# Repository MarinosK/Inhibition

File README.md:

### Inhibition ###

Installation | Workshop (c) 2016
by Marinos Koutsomichalis <marinos@marinoskoutsomichalis.com>

Code and hardware designs are distributed under the Attribution-NonCommercial-ShareAlike 3.0 Unported Creative Commons Licence (details here: http://creativecommons.org/licenses/by-nc-sa/3.0/deed.en_US).

> EVERYTHING IN THIS BUNDLE IS DISTRIBUTED AS IS WITH NO GUARANTEE OF FUNCTIONALITY OR RELEVANCE TO THIRD PARTY PROJECTS - THE DEVELOPER IS NOT TO BE HELD RESPONSIBLE FOR PERSONAL INJURIES, HARDWARE, FINANCIAL, OR ANY OTHER LOSSES AND IN GENERAL FOR ANY MISFORTUNATE EVENT CAUSED BY THE DESCRIBED SOFTWARE/HARDWARE OR IN THE PROCESS OF ATTEMPTING TO IMPLEMENT IT. IF YOU DON'T AGREE WITH THE AFOREMENTIONED YOUR ARE NOT ALLOWED TO USE THE MATERIAL PROVIDED HEREIN

# This bundle comprises #

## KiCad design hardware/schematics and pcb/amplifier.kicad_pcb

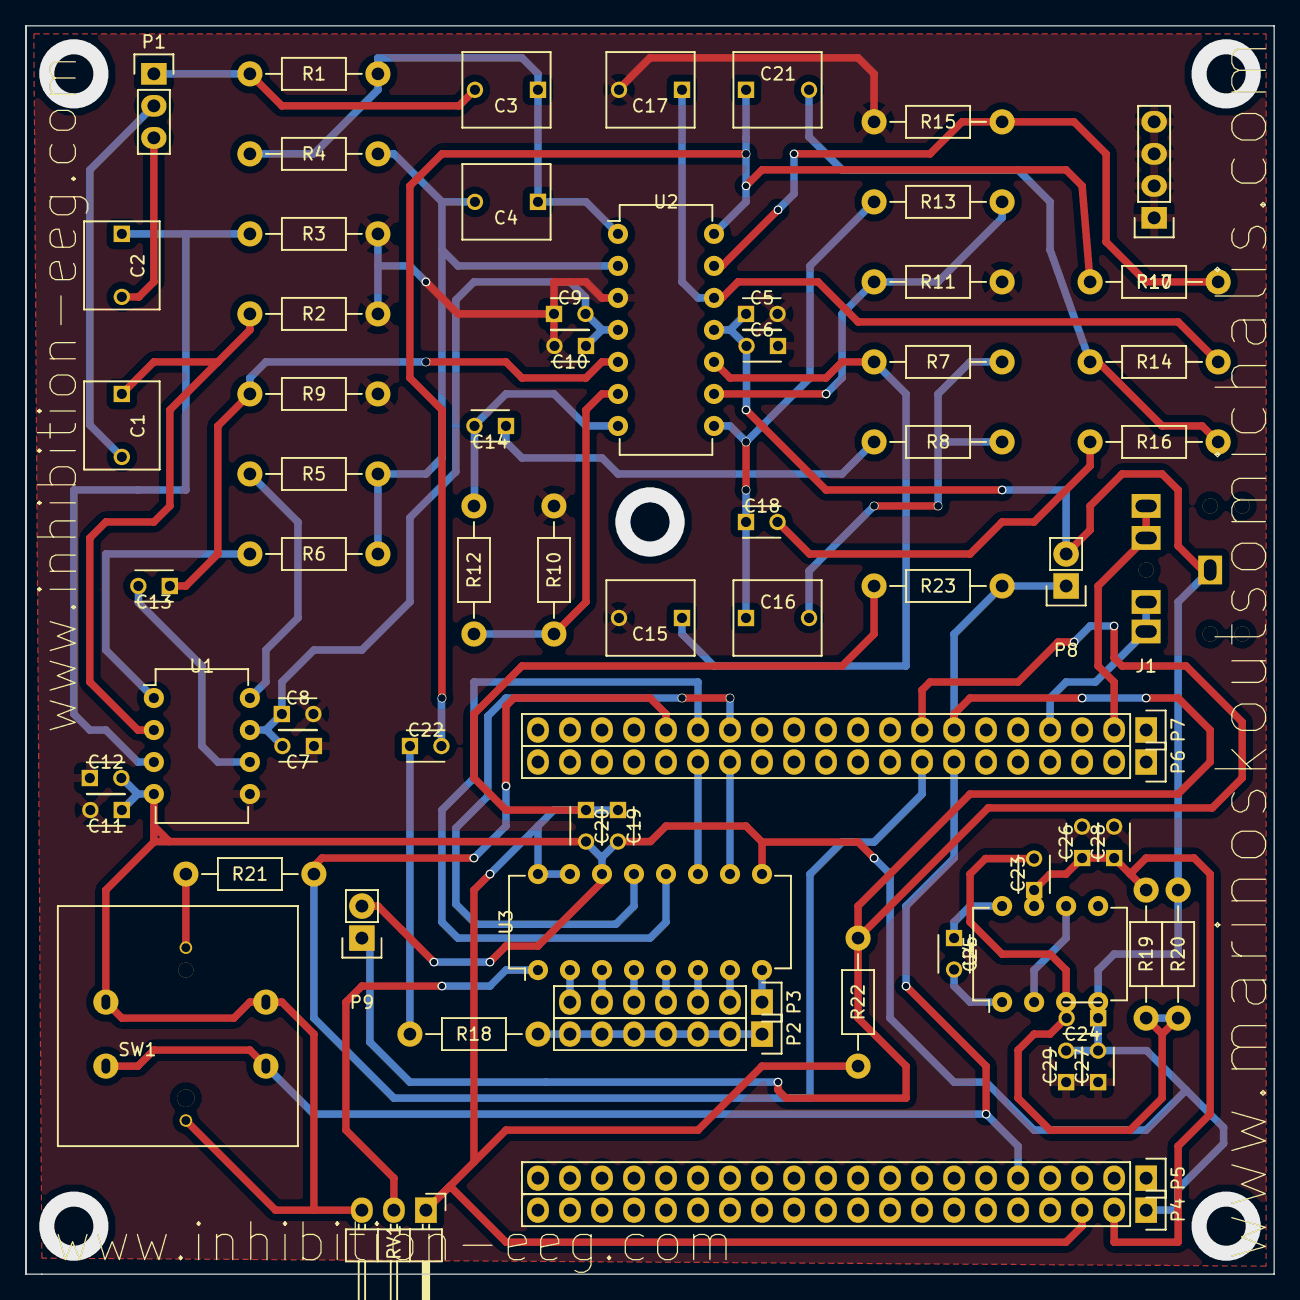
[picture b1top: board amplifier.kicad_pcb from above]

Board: 2 copper layers, 99.1 x 99.1 mm, 69 parts (0 on the bottom side), 51 nets.

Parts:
C1, C2: 0.01μ; C_Rect_L7_W6_P5
C3, C4: 1n; C_Rect_L7_W6_P5
C5, C7, C9, C11, C19: 0.01μ; C_Disc_D3_P2.5
C6, C8, C10, C12, C20: 0.33μ; C_Disc_D3_P2.5
C13, C14, C18, C22, C28, C29: 10μ; C_Disc_D3_P2.5
C15, C17: 0.47μ; C_Rect_L7_W6_P5
C16, C21: 0.82μ; C_Rect_L7_W6_P5
C23, C24: .01μ; C_Disc_D3_P2.5
C25: 1n; C_Disc_D3_P2.5
C26, C27: 1μ; C_Disc_D3_P2.5
J1: JACK_2P; BARREL_JACK
P1: CONN_01X03; Pin_Header_Straight_1x03
P2, P3: CONN_01X07; Pin_Header_Straight_1x07
P4, P5, P6, P7: CONN_01X20; Pin_Header_Straight_1x20
P8, P9: CONN_01X02; Pin_Header_Straight_1x02
P10: CONN_01X04; Pin_Header_Straight_1x04
R1, R4: 100K; Resistor_Horizontal_RM10mm
R2, R3: 15M; Resistor_Horizontal_RM10mm
R5, R6, R18: 220; Resistor_Horizontal_RM10mm
R7, R8, R9, R10, R11, R14, R15, R16, R20: 10K; Resistor_Horizontal_RM10mm
R12: 890K; Resistor_Horizontal_RM10mm
R13: 1.8; Resistor_Horizontal_RM10mm
R17: .6; Resistor_Horizontal_RM10mm
R19: 15K; Resistor_Horizontal_RM10mm
R21: 10; Resistor_Horizontal_RM10mm
R22, R23: 1K; Resistor_Horizontal_RM10mm
RV1: POT; Pin_Header_Angled_1x03
SW1: Switch_DPST; Switch_LED
U1: AD620; DIP-8_W7.62mm
U2: LM324; DIP-14_W7.62mm
U3: MCP3008; DIP-16_W7.62mm
U4: CA3140; DIP-8_W7.62mm

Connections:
GND: C5.2, C6.1, C7.1, C8.2, C9.1, C10.2, C11.2, C12.1, C15.2, C17.2, C26.2, C27.1, C28.2, C29.1, P10.1, P10.2, P10.3, P10.4, R2.2, R3.2, R9.2, R10.2, R11.2, R15.2, U1.5, U2.3, U4.2, U4.6
unnamed: C1.1, R2.1, U1.2
unnamed: C1.2, P1.2
unnamed: C2.1, R3.1, U1.3
unnamed: C2.2, P1.3
unnamed: C3.1, C4.1, R1.1, R4.1, U2.1
unnamed: C3.2, P1.1, R1.2
unnamed: C4.2, R4.2, R5.2, R6.1, U2.2
unnamed: C13.1, R9.1, U2.5
unnamed: C13.2, U1.6
unnamed: C14.1, R8.2
unnamed: C14.2, R12.1, U2.7
unnamed: C15.1, R7.1, U2.10
unnamed: C16.1, C18.1, R13.1, U2.8
unnamed: C16.2, R7.2, R8.1
unnamed: C17.1, R14.2, U2.12
unnamed: C18.2, R16.2
unnamed: C19.1, C20.1, P4.3, R22.2, R23.2, RV1.1, U3.15, U3.16
unnamed: C21.1, C22.2, R17.1, U2.14
unnamed: C21.2, R14.1, R16.1
unnamed: C22.1, R18.1
unnamed: C23.2, C24.2, R19.2, R20.1, U4.3
unnamed: C25.1, U4.8
unnamed: C25.2, U4.1
unnamed: J1.1, P7.4
unnamed: J1.3, P7.2
unnamed: P2.1, P2.2, P2.3, P2.4, P2.5, P2.6, P2.7, R18.2
unnamed: P3.1, U3.8
unnamed: P3.2, U3.7
unnamed: P3.3, U3.6
unnamed: P3.4, U3.5
unnamed: P3.5, U3.4
unnamed: P3.6, U3.3
unnamed: P3.7, U3.2
unnamed: P5.5, SW1.1, SW1.3
unnamed: P6.14, U3.10
unnamed: P6.15, U3.11
unnamed: P7.7, P8.1, R23.1
unnamed: P7.8, P9.1, R22.1
unnamed: P7.14, U3.13
unnamed: P7.15, U3.12
unnamed: P7.16, R21.2
unnamed: R5.1, U1.8
unnamed: R6.2, U1.1
unnamed: R10.1, R12.2, U2.6
unnamed: R11.1, R13.2, U2.9
unnamed: R15.1, R17.2, U2.13
unnamed: R21.1, SW1.5
unnamed: RV1.2, U3.1
VCC: C7.2, C8.1, C9.2, C10.1, C23.1, C26.1, C28.1, P4.2, R19.1, U1.7, U2.4, U4.7
VEE: C5.1, C6.2, C11.1, C12.2, C19.2, C20.2, C24.1, C27.2, C29.2, J1.2, P4.1, P8.2, P9.2, R20.2, RV1.3, SW1.2, SW1.4, SW1.6, U1.4, U2.11, U3.9, U3.14, U4.4

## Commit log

2016-10-23 first commit: software is more or less OK (I need to make it less CPU-expensive to avoid glitches and to add machine learning suppport), hardware the same (need to fix a couple of errors in the pcb a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
2016-10-23 sc-code: changed routines to run on the AppClock to save some resources
2016-10-26 updated the archicture so that I can now implement some ml algorithm - also minor changes elsewhere
2016-10-26 I have reorganised a bit the folders
2016-10-27 first working version with audio, eeg and ML - might need some fine tuning to make it sound the way I want, needs a lot of testing and needs a lot of code clean-up and commentary
2016-10-28 fine-tuning and minor changes
2016-10-29 more minor changes and fine-tuning
2016-10-29 I have made the system slightly more responsive
2016-11-09 fixed a couple of things in the pcb and added 3d models
2016-11-09 more fixes in the pcb
2016-11-11 corrected the set-up instructions
2016-12-01 updated instructions and added a new simpler code bundle for the workshops (this is still a a bit dirty tho)
2016-12-01 uses Pitch instead of Tartini
2016-12-01 corrected a couple of things in the set_up chip
2016-12-01 corrected more things
2016-12-01 minor changes
2016-12-06 simplified the code for the workshops a bit
2016-12-06 minor changes in the instructions
2016-12-08 changed volume
2016-12-26 replaced a problematic 3d model
